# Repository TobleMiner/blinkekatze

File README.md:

Blinkekatze 😺
=============

This is a replacement PCB for one version of cat themed night lights available via various online retailers.

It adds a number of RGB LEDs, sensors and wireless connectivity, enabling an interactive light display synchronized over a large number of Blinkekatzen.

Inspired by the wonderful [derf](https://github.com/derf)

# Architecture

The Blinkekatze is comprised of three PCBs:
 - The main board (this directory)
 - The USB board (located in [/usb-board](/usb-board))
 - The original power- and mode-switch board from the nightlight

## Mainboard

The main board contains most elements critical to device operation. At its heart is an ESP32-C3 for control.

The ESP32-C3 is accompanied by the following peripherals:
 - 16 super bright, individually controllable RGB LEDs (effectively ~12bit RGB color control)
 - High precision battery gauge for accurate capacity tracking and runtime estimation
 - Accelerometer and barometer to detect user interaction
 - Ambient light sensor enabling automatic brightness control
 - Efficient buck-mode battery charger

The main board also includes a MEMS PDM microphone that could be used for audio synchronization of lighting effects.
However note the ESP32-C3 is missing hardware PDM to PCM conversion capability.

## USB board

The USB board replaces the original board used for charging in the nightlight. It offers USB connectivity to the
ESP32-C3 and contains two indicator LEDs visible through the bottom of the Blinkekatze.

To facilitate easy, solderless assembly mainboard and USB board are connected by a 5cm long 16 pin flat flex cable with opposite side contacts.

# Ordering PCBs

All PCBs required to build Blinkekatzen can be ordered fully assembled from JLCPCB. The necessary fabrication files are located in [/fab](/fab) for
the main board and [/usb-board/fab](/usb-board/fab). It is recommended to always use the latest revision available in those folders.  
When ordering the PCBs they should be ordered as 1.6mm 4 layers for the mainboard and 1.6mm 2 layers for the USB board.

## PCB assembly

In addition to the bare PCBs JLCPCB also offers an assembly service. The BOM and component centroid files required for assembly are also located in
[/fab](/fab) and [/usb-board/fab](/usb-board/fab) respectively.  
When ordering assembly for the main PCB cost can be reduced significantly by choosing to populate only the top side of the PCB and later assembling
the battery contacts (BTT1 and BTT2) on the bottom side by yourself manually. Those are the only parts on the bottom side of the PCB. Also microphone
U6 is best left unpopulated since a lack of proper PDM to PCM support on the ESP32-C3 makes it mostly unusable.

### Additional required electronic components

Apart from the components assembled by JLCPCB the following parts are required:  
 - 2x MYOUNG MY-18650-01 battery contacts (if not assembled by JLCPCB, see previous section)
 - 1x 5cm 16pin 0.5mm pitch flat flex cable (e.g. C5151983 on LCSC)
 - 1x 18650 battery (Samsung INR18650-35E recommended)

### JLCPCB assembly component availability

Sometimes components required for assembly are out of stock at JLCPCB. In this case the parts have to be ordered fist through
JLCPCB's parts preorder service. Usually all required parts can be preordered in small quantities and will be available within
a couple of days.

# Assembling the Blinkekatzen

## Preparing the PCB

If the battery contacts were not assembled through JLCPCB they need to be soldered. The overall fit of the battery is best with the
contacts installed as far apart as possible within the throughholes. Special care should be taken to ensure the battery contacts are
not soldered at an angle but lie flat on the PCB. Otherwise the battery might not snap into the contacts properly.

## Preparing the housing

In the first step the rubber boot needs to be removed. The puck containing all electronics can either be pulled out to the bottom or
first pushed into the puck and then removed.  
Next the transparent diffuser on top of the puck can be removed by undoing the three screws (relatively long and skinny #0 Phillips
head screwdriver required) and pulling up on the diffuser.  

## Removing the original PCBs

The original PCB is held in place with two screws. After undoing the screws the PCB can be pivoted to the side and the battery unplugged.  
The original USB board also needs to be removed by undoing the two screws holding it in place.  
Finally the PCB can be freed by desoldering the six connections on the original main PCB that go to the switch board in the bottom of the case.
Since the switch board will be reused desoldering rather than cutting the wire can save some time later.  

## Modifying the case

After removal of the original main PCB the case needs to be modified slightly to accommodate the new battery. To make space for the new battery
and battery holder snip out the two thin plastic walls with the half circle shaped cutouts the old battery was resting on using flush cutters.

## Installing the USB board

The first new component to be installed in the housing is the new USB board. Since this board will be installed with the USB connector and flat
flex connector facing down the flat flex cable needs to be connected to this board first. To connect the flat flex cable the latch on the
connector must be flipped up and the cable then inserted with the contacts facing down. The cable is then secured by closing the latch again.  
Now the USB board can be installed in the housing and secured in place with the two screws.

## Installing the new main PCB

As a first step the two outermost contacts of the ribbon cable earlier desoldered from the original main PCB are soldered to the power key header
J1 on the new main PCB (labeled PWR_ON and VBAT, polarity does not matter). Then the battery is installed (here polarity does very much matter). **NEVER**
may batteries without or with a damaged insulating sleeve be used with this device. The battery contacts will short out such batteries!  
After folding back the flat flex cable so it remains free and is not trapped under the battery the new main PCB is fixed in place with two screws.  
As a final step the flat flex cable is now installed into the flat flex connector on the new main PCB in the same manner as on the USB board.

## Firmware flashing

Please see [blinkekatze-firmware](https://github.com/TobleMiner/blinkekatze-firmware) for details on firmware flashing.

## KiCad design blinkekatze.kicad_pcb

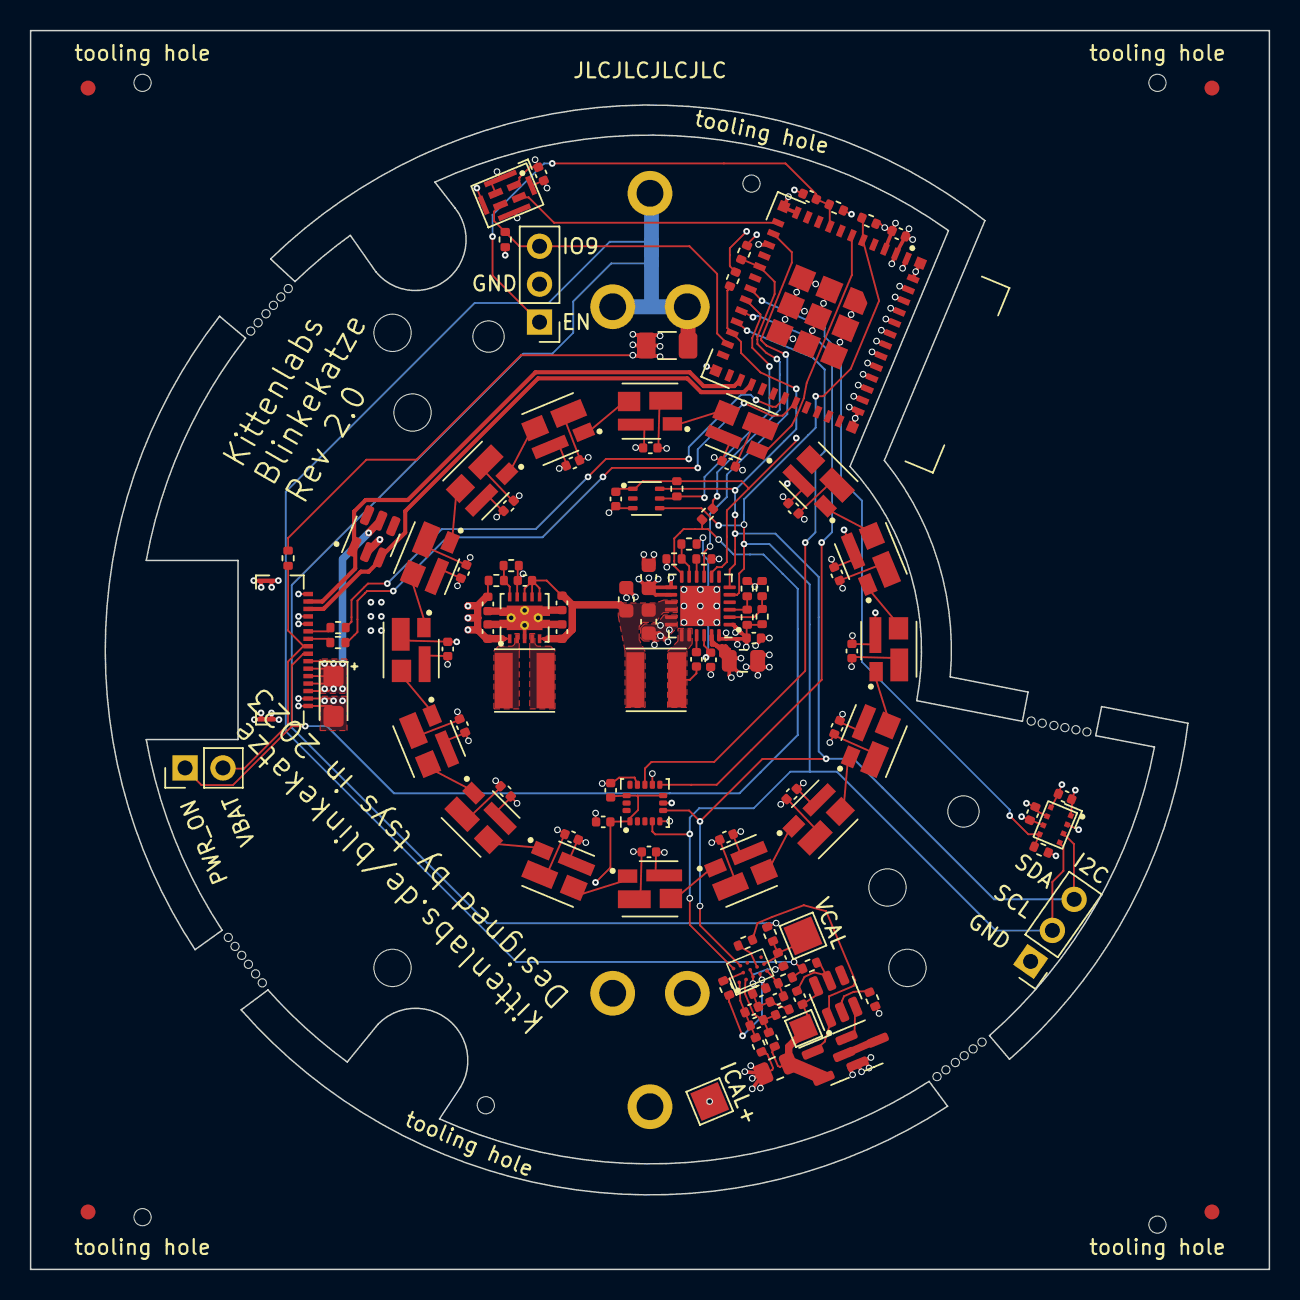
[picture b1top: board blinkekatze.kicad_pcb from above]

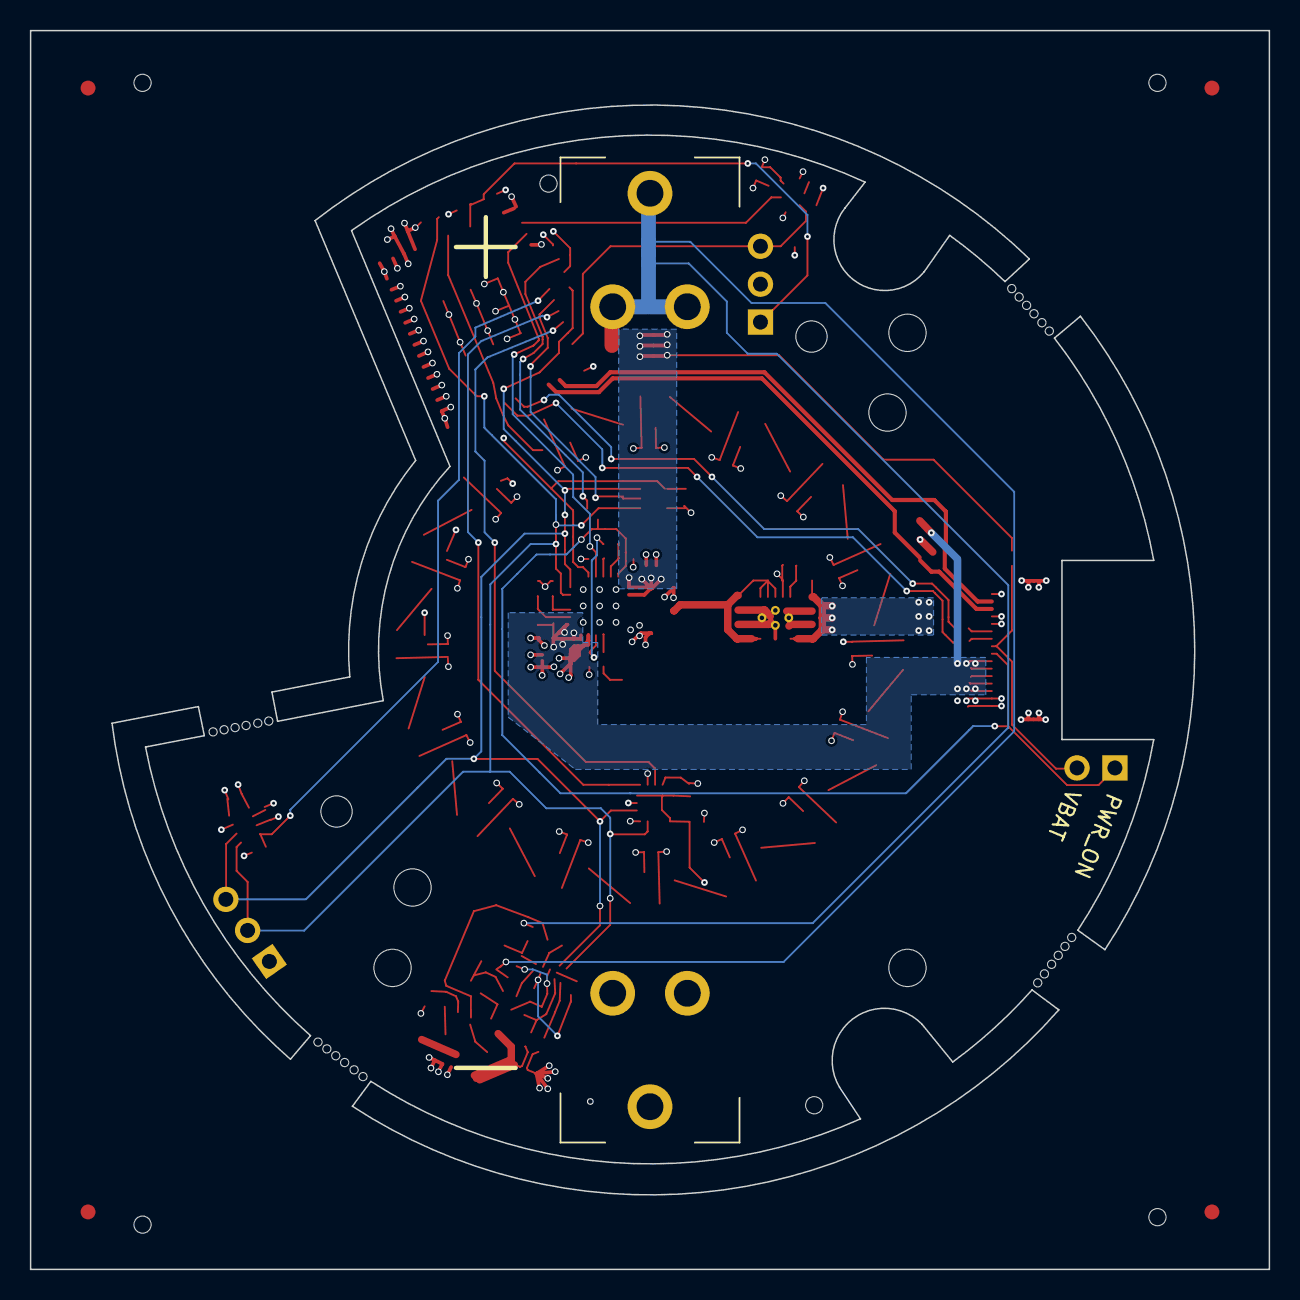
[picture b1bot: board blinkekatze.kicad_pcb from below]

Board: 4 copper layers, 83.0 x 83.0 mm, 122 parts (2 on the bottom side), 66 nets.

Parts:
BTT1: B+; MY-18650-01_flat-top
BTT2: B-; MY-18650-01_flat-top
C1, C2, C3, C4, C5, C6, C7, C8, C9, C10, C11, C12, C13, C14, C15, C16, C20, C21, C22, C23, C24, C26, C27, C73: 100nF; C_0402_1005Metric
C17: 10uF; CP_EIA-3216-18_Kemet-A
C18, C19, C25, C33, C66, C67, C68, C69, C70: 1uF; C_0402_1005Metric
C28: 22uF; C_0805_2012Metric
C29: 4.7uF; C_0402_1005Metric
C30, C31, C32: 10uF; C_0603_1608Metric
C65, C71, C72, C74, C75: 10uF; C_0402_1005Metric
D1, D2, D3, D4, D5, D6, D7, D8, D9, D10, D11, D12, D13, D14, D15, D16: SK6812MINI-012; XXXX12-X1
F1: 4A; Fuse_1206_3216Metric
H1: Left peg; MountingHole_2.1mm
H2: Right peg; MountingHole_2.1mm
H3: Left screw; MountingHole_2.5mm
H4: Right screw; MountingHole_2.5mm
H5, H6: Tooling hole; ToolingHole_JLCSMT
H7: LU; MountingHole_2.5mm
H8: RL; MountingHole_2.5mm
H9: LL; MountingHole_2.5mm
J1: Power key; PinHeader_1x02_P2.54mm_Vertical
J2: Strapping; PinHeader_1x03_P2.54mm_Vertical
J3: I2C; PinHeader_1x03_P2.54mm_Vertical
J4: USB board; 0.5K-QX-16PWB_16Pin_0.5mm
L2, L4: 2.2uH; L_Taiyo-Yuden_MD-4040
Q1, Q2: AO3400A; SOT-23
R1, R9, R13, R14, R15, R16, R17, R18, R21, R22, R43: 10k; R_0402_1005Metric
R2, R5, R6, R7, R10, R11, R12: 100R; R_0402_1005Metric
R3: 220R; R_0402_1005Metric
R4: 10mR; R_0805_2012Metric
R8: 1k; R_0402_1005Metric
R19, R20: 330; R_0402_1005Metric
R23, R44: 100k; R_0402_1005Metric
R45, R46: 4.7k; R_0402_1005Metric
R48: 0R; R_0402_1005Metric
R49: DNP; R_0402_1005Metric
TP3: ICAL+; TestPoint_Pad_2.0x2.0mm
TP4: VCAL; TestPoint_Pad_2.0x2.0mm
TP5: ICAL-; TestPoint_Pad_1.5x1.5mm
U1: ESP32-C3-MINI-1
U2: BQ27546; DSBGA-15_BQ27546_I2C_1.95x2.6mm_P0.5mm
U3: SRV05-4; SOT-23-6
U4: FM2113; SOT-23-6
U5: SPL06-001; LGA-8_2x2.5mm_P0.65mm
U6: ST_HCLGA-4LD_3x4mm
U7: LTR-303ALS-01; Lite-On_LTR-303ALS-01
U8: BQ24295; QFN-24-1EP_4x4mm_P0.5mm_EP2.7x2.7mm
U9: TPS63001; Texas_DRC0010J_ThermalVias.3
U10: LIS3DH; LGA-16_3x3mm_P0.5mm_LayoutBorder3x5y

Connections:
+3V3: C18.2, C19.1, C65.1, C67.1, C68.1, C69.2, C70.1, C74.2, C75.2, R21.1, R22.1, R43.1, R44.1, R45.1, R46.1, R48.1, U1.3 (3V3), U5.2 (CSB), U5.6 (VDDIO), U5.8 (VDD), U6.1 (VDD), U7.1 (VDD), U8.8 (OTG), U9.1 (VOUT), U10.1 (VDD_IO), U10.8 (CS), U10.14 (VDD)
+BATT: BTT1.1, F1.1, R7.1, R10.1, R11.1
/Battery/BAT+: C32.1, F1.2, R2.2, U8.13 (BAT), U8.14 (BAT)
/Battery/DSG: R12.2, U2.D2 (CE)
/Battery/SCL: J3.2, R46.2, U1.5 (IO2), U2.A3 (SCL), U5.4 (SCK), U7.4 (SCL), U8.5 (SCL), U10.4 (SCL/SPC)
/Battery/SDA: J3.3, R45.2, U1.22 (IO8), U2.B3 (SDA), U5.3 (SDA), U7.6 (SDA), U8.6 (SDA), U10.6 (SDA/SDI/SDO)
/Charger/PWR_ON: J1.1, J4.9, R1.1, U8.12 (QON)
/Charger/VLED: C1.2, C2.2, C3.2, C4.2, C5.2, C6.2, C7.2, C8.2, C9.2, C10.2, C11.2, C12.2, C13.2, C14.2, C15.2, C16.2, C28.1, D1.2 (VDD), D2.2 (VDD), D3.2 (VDD), D4.2 (VDD), D5.2 (VDD), D6.2 (VDD), D7.2 (VDD), D8.2 (VDD), D9.2 (VDD), D10.2 (VDD), D11.2 (VDD), D12.2 (VDD), D13.2 (VDD), D14.2 (VDD), D15.2 (VDD), D16.2 (VDD), U8.23 (PMID)
/Charger/VSYS: C30.1, C31.1, C71.2, C72.2, C73.2, L2.2, U8.15 (SYS), U8.16 (SYS), U9.5 (VIN), U9.6 (EN), U9.7 (PS/SYNC), U9.8 (VINA)
/Charger/~CHARGE_ENABLE: U1.13 (IO1), U8.9 (~CE)
/LEDs/DIN: D12.1 (DIN), U1.6 (IO3)
/Logic/EN: C66.2, J2.1, R44.2, U1.8 (EN)
/Logic/IO9: J2.3, R43.2, U1.23 (IO9), U6.3 (CLK)
/Logic/LED1: J4.6, R20.1
/Logic/LED2: J4.7, R19.1
/Logic/USB_D+: J4.3, U1.27 (IO19/D+), U3.3 (IO2)
/Logic/USB_D-: J4.2, U1.26 (IO18/D-), U3.1 (IO1)
/USB/VBAT: J1.2, J4.8, R2.1
GND: C1.1, C2.1, C3.1, C4.1, C5.1, C6.1, C7.1, C8.1, C9.1, C10.1, C11.1, C12.1, C13.1, C14.1, C15.1, C16.1, C17.2, C18.1, C19.2, C28.2, C29.2, C30.2, C31.2, C32.2, C33.1, C65.2, C66.1, C67.2, C68.2, C69.1, C70.2, C71.1, C72.1, C73.1, C74.1, C75.1, D1.4 (VSS), D2.4 (VSS), D3.4 (VSS), D4.4 (VSS), D5.4 (VSS), D6.4 (VSS), D7.4 (VSS), D8.4 (VSS), D9.4 (VSS), D10.4 (VSS), D11.4 (VSS), D12.4 (VSS), D13.4 (VSS), D14.4 (VSS), D15.4 (VSS), D16.4 (VSS), J2.2, J3.1, J4.1, J4.4, J4.5, J4.15, J4.16, J4.MP (MountPin), Q2.2 (S), R3.2, R8.1, R14.2, R15.2, R16.2, R23.2, R49.2, U1.1 (GND), U1.2 (GND), U1.11 (GND), U1.14 (GND), U1.36 (GND), U1.37 (GND), U1.38 (GND), U1.39 (GND), U1.40 (GND), U1.41 (GND), U1.42 (GND), U1.43 (GND), U1.44 (GND), U1.45 (GND), U1.46 (GND), U1.47 (GND), U1.48 (GND), U1.49 (GND), U1.50 (GND), U1.51 (GND), U1.52 (GND), U1.53 (GND), U3.2 (VN), U5.1 (GND), U5.7 (GND), U6.2 (L/R), U6.5 (GND), U7.3 (GND), U8.17 (PGND), U8.18 (PGND), U8.25 (PGND), U9.3 (PGND), U9.9 (GND), U9.11 (PGND), U10.5 (GND), U10.7 (SDO/SA0), U10.10 (GND), U10.12 (GND)
GND1: BTT2.1, C20.1, C22.2, C23.2, C24.2, C25.1, R4.1, R5.1, TP3.1, U2.C1 (VSS), U2.C2 (VSS)
unnamed: C27.1, L2.1, U8.19 (SW), U8.20 (SW)
unnamed: D1.1 (DIN), D16.3 (DOUT)
unnamed: D1.3 (DOUT), D2.1 (DIN)
unnamed: D2.3 (DOUT), D3.1 (DIN)
unnamed: D3.3 (DOUT), D4.1 (DIN)
unnamed: D4.3 (DOUT), D5.1 (DIN)
unnamed: D5.3 (DOUT), D6.1 (DIN)
unnamed: D6.3 (DOUT), D7.1 (DIN)
unnamed: D7.3 (DOUT), D8.1 (DIN)
unnamed: D8.3 (DOUT), D9.1 (DIN)
unnamed: D9.3 (DOUT), D10.1 (DIN)
unnamed: D10.3 (DOUT), D11.1 (DIN)
unnamed: D12.3 (DOUT), D13.1 (DIN)
unnamed: D13.3 (DOUT), D14.1 (DIN)
unnamed: D14.3 (DOUT), D15.1 (DIN)
unnamed: D15.3 (DOUT), D16.1 (DIN)
unnamed: Q1.3 (D), Q2.3 (D)
unnamed: Q1.1 (G), R12.1, U4.1 (DO)
unnamed: C26.1, Q1.2 (S), R4.2, R6.1, TP5.1, U4.6 (VSS)
unnamed: Q2.1 (G), U4.3 (CO)
unnamed: U1.12 (IO0), U6.4 (DATA)
unnamed: R21.2, U1.18 (IO4), U5.5 (SDO)
unnamed: R22.2, U1.19 (IO5), U7.5 (INT)
unnamed: U1.20 (IO6), U10.9 (INT2)
unnamed: U1.21 (IO7), U10.11 (INT1)
unnamed: R1.2, R23.1, U1.16 (IO10)
unnamed: R20.2, U1.30 (RXD0)
unnamed: R19.2, U1.31 (TXD0)
unnamed: C23.1, R7.2, TP4.1, U2.E2 (BAT)
unnamed: C24.1, R10.2, U2.E1 (REGIN)
unnamed: C21.2, C22.1, R6.2, U2.B1 (SRN)
unnamed: C20.2, C21.1, R5.2, U2.A1 (SRP)
unnamed: R9.1, U2.B2 (TS)
unnamed: C25.2, R9.2, U2.D1 (VCC)
unnamed: C26.2, R11.2, U4.5 (VDD)
unnamed: R8.2, U4.2 (VM)
unnamed: C27.2, U8.21 (BTST)
unnamed: R15.1, R17.2, U8.2 (D+)
unnamed: R16.1, R18.2, U8.3 (D-)
unnamed: R3.1, U8.10 (ILIM)
unnamed: C29.1, R13.2, U8.22 (REGN)
unnamed: R13.1, R14.1, U8.11 (TS)
unnamed: R48.2, R49.1, U9.10 (FB)
unnamed: L4.1, U9.4 (L1)
unnamed: L4.2, U9.2 (L2)
VBUS: C17.1, C33.2, J4.10, J4.11, J4.12, J4.13, J4.14, R17.1, R18.1, U3.5 (VP), U8.1 (VBUS), U8.24 (VBUS)

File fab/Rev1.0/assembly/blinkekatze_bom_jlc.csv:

"Comment","Designator","Footprint","LCSC Part #"
"B+","BTT1","MY-18650-01","C2979183"
"B-","BTT2","MY-18650-01","C2979183"
"100nF","C1,C2,C3,C4,C5,C6,C7,C8,C9,C10,C11,C12,C13,C14,C15,C16,C73,C20,C21,C22,C23,C24,C26,C27","C_0402_1005Metric","C1525"
"10uF","C17","CP_EIA-3216-18_Kemet-A","C7171"
"1uF","C18,C19,C66,C67,C68,C69,C70,C25,C33","C_0402_1005Metric","C52923"
"22uF","C28","C_0805_2012Metric","C45783"
"4.7uF","C29","C_0402_1005Metric","C23733"
"10uF","C30,C31,C32","C_0603_1608Metric","C19702"
"10uF","C65,C71,C72,C74,C75","C_0402_1005Metric","C15525"
"SK6812MINI-012","D1,D2,D3,D4,D5,D6,D7,D8,D9,D10,D11,D12,D13,D14,D15,D16","XXXX12-X1","C2886570"
"4A","F1","Fuse_1206_3216Metric","C187596"
"2.2uH","L4,L2","L_Taiyo-Yuden_MD-4040","C98361"
"AO3400A","Q1,Q2","SOT-23","C20917"
"10k","R1,R43,R9,R13,R14,R15,R16,R17,R18","R_0402_1005Metric","C25744"
"100R","R2,R5,R6,R7,R10,R11,R12","R_0402_1005Metric","C25076"
"150R","R3","R_0402_1005Metric","C25082"
"10mR","R4","R_0805_2012Metric","C5185583"
"1k","R8","R_0402_1005Metric","C11702"
"330","R19,R20","R_0402_1005Metric","C25104"
"100k","R44","R_0402_1005Metric","C25741"
"4.7k","R45,R46","R_0402_1005Metric","C25900"
"0R","R48","R_0402_1005Metric","C17168"
"ESP32-C3-MINI-1","U1","ESP32-C3-MINI-1","C2838502"
"BQ27546","U2","DSBGA-15_BQ27546_I2C_1.95x2.6mm_P0.5mm","C528629"
"SRV05-4","U3","SOT-23-6","C85364"
"FM2113","U4","SOT-23-6","C2832124"
"SPL06-001","U5","LGA-8_2x2.5mm_P0.65mm","C2684428"
"~","U6","ST_HCLGA-4LD_3x4mm","C503097"
"LTR-303ALS-01","U7","Lite-On_LTR-303ALS-01","C364577"
"BQ24295","U8","QFN-24-1EP_4x4mm_P0.5mm_EP2.7x2.7mm","C165144"
"TPS63001","U9","Texas_DRC0010J_ThermalVias.3","C28060"
"LIS3DH","U10","LGA-16_3x3mm_P0.5mm_LayoutBorder3x5y","C15134"

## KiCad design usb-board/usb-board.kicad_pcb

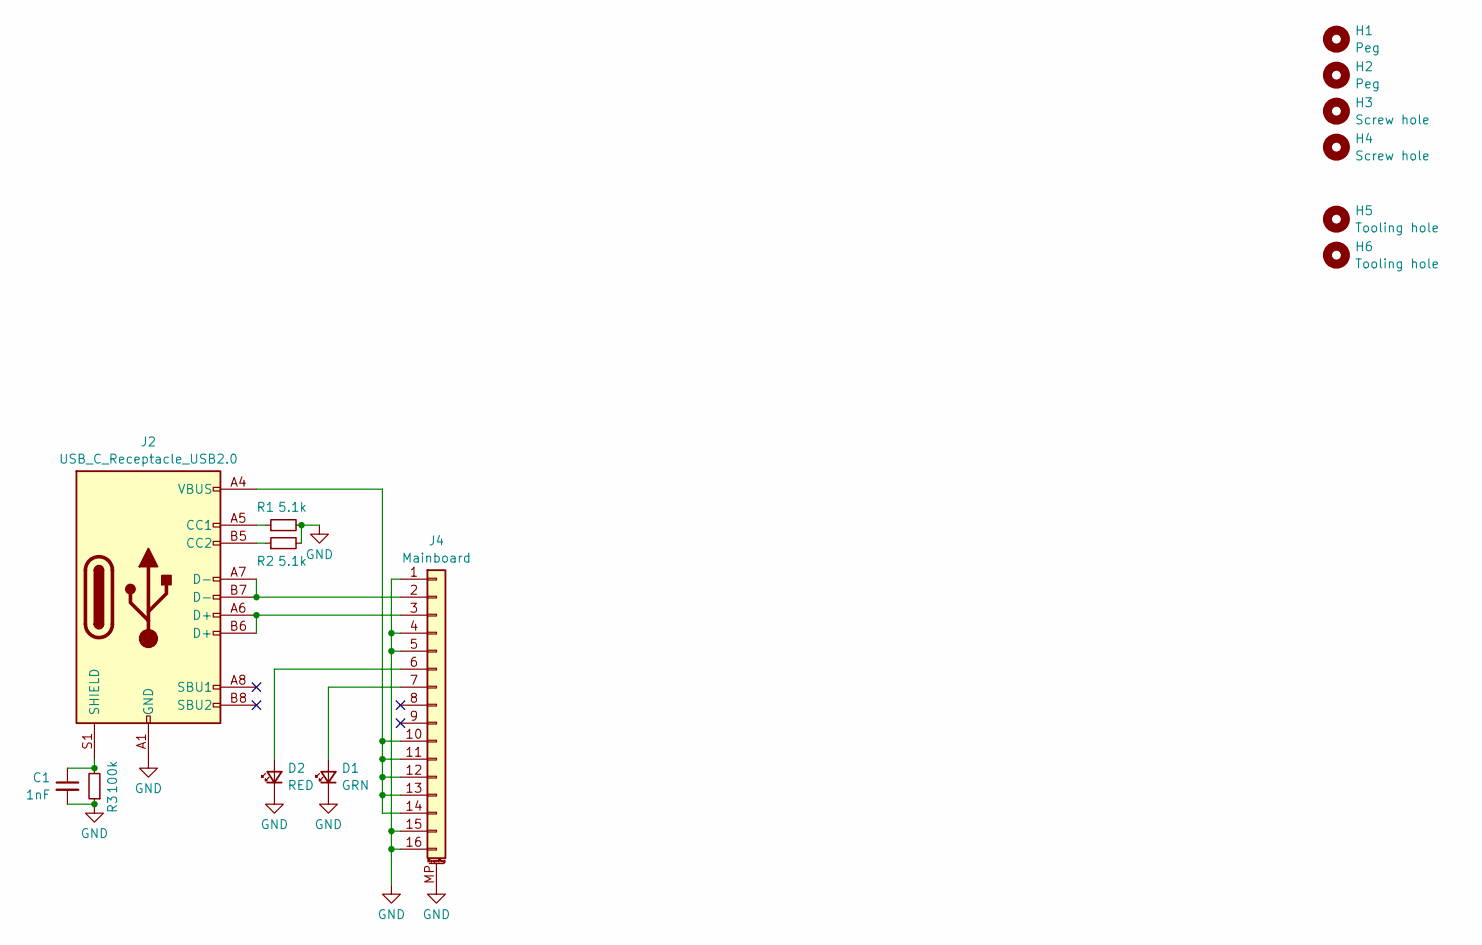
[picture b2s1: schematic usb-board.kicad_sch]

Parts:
C1: 1nF; C_1206_3216Metric; LCSC C9196
D1: GRN; LED_0603_1608Metric; LCSC C72043
D2: RED; LED_0603_1608Metric; LCSC C2286
H1, H2: Peg; MountingHole_2.1mm
H3, H4: Screw hole; MountingHole_2.5mm
H5, H6: Tooling hole; ToolingHole_JLCSMT
J2: USB_C_Receptacle_USB2.0; USB_C_Receptacle_Palconn_UTC16-G; LCSC C167321
J4: Mainboard; 0.5K-QX-16PWB_16Pin_0.5mm; LCSC C2919481
R1, R2: 5.1k; R_0402_1005Metric; LCSC C25905
R3: 100k; R_0805_2012Metric; LCSC C149504

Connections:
GND: C1.2, D1.1 (K), D2.1 (K), J2.A1 (GND), J2.A12 (GND), J2.B1 (GND), J2.B12 (GND), R1.2, R2.2, R3.1; also elsewhere on the board
unnamed 1: D1.2 (A); also elsewhere on the board
unnamed 2: D2.2 (A); also elsewhere on the board
unnamed: J2.A5 (CC1), R1.1
unnamed: J2.B5 (CC2), R2.1
unnamed: C1.1, J2.S1 (SHIELD), R3.2
unnamed 6: J2.A7 (D-), J2.B7 (D-); also elsewhere on the board
unnamed 7: J2.A6 (D+), J2.B6 (D+); also elsewhere on the board
unnamed 8: J2.A4 (VBUS), J2.A9 (VBUS), J2.B4 (VBUS), J2.B9 (VBUS); also elsewhere on the board

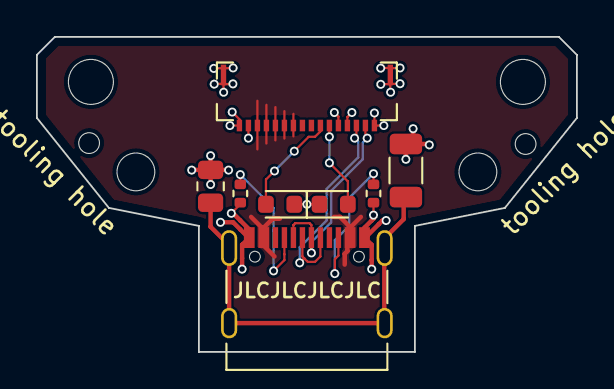
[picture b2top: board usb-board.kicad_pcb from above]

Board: 2 copper layers, 30.0 x 17.5 mm, 14 parts (0 on the bottom side), 9 nets.

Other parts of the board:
J3: Mainboard; 0.5K-QX-16PWB_16Pin_0.5mm

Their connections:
GND: J3.1, J3.4, J3.5, J3.15, J3.16, J3.MP (MountPin); also elsewhere on the board
unnamed 1: J3.7; also elsewhere on the board
unnamed 2: J3.6; also elsewhere on the board
unnamed 6: J3.2; also elsewhere on the board
unnamed 7: J3.3; also elsewhere on the board
unnamed 8: J3.10, J3.11, J3.12, J3.13, J3.14; also elsewhere on the board

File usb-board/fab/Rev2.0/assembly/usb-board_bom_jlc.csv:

"Comment","Designator","Footprint","LCSC Part #"
"1nF","C1","C_1206_3216Metric","C9196"
"GRN","D1","LED_0603_1608Metric","C72043"
"RED","D2","LED_0603_1608Metric","C2286"
"USB_C_Receptacle_USB2.0","J2","USB_C_Receptacle_Palconn_UTC16-G","C167321"
"Mainboard","J3","0.5K-QX-16PWB_16Pin_0.5mm","C2919481"
"5.1k","R1,R2","R_0402_1005Metric","C25905"
"100k","R3","R_0805_2012Metric","C149504"

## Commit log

2023-09-08 Add gauge schematic and partial charger schematic
2023-09-08 Fix duplicate pin assignment on pressure sensor
2023-09-08 Finish preliminary charger and logic schematic
2023-09-08 Aesthetic top level schematic fixes
2023-09-10 Add list of 1S charger chips
2023-09-11 Finish rough layout
2023-09-11 Add 3D model to battery gauge
2023-09-11 Hide silkscreen designators
2023-09-11 JLCPCB DFM
2023-09-11 Add accelerometer
2023-09-11 Add copper fill keepouts below poorly shielded inductors
2023-09-11 Add pin 1 marker to ambient light sensor and accelerometer
2023-09-11 Add I2C test connector
2023-09-11 Add battery polarity indicators
2023-09-11 Remove duplicate pin 36 from ESP32-C3-MINI-1
2023-09-11 Reduce battery protection IC VDD impedance
    Reduce from 470R to 100R in line with manufacturers recommendation
2023-09-11 Update ESP32-C3-MINI-1 symbol in schematic
2023-09-11 Fix incorrect vertical pad spacing on SK6812-MINI-X1 footprint
2023-09-11 Update SK6812-MINI-X1 footprints
2023-09-11 Add simple USB board replacement
2023-09-11 usb-board: improve VBUS connection
2023-09-11 Add pin 1 marker to barometric pressure sensor
2023-09-13 Add informational comment on input current limit to schematic
2023-10-11 lib: add flat-top variant of MY-18650-01 battery holder
2023-10-11 usb-board: add silkscreen markings
2023-10-11 battery: use flat top battery holder
2023-10-11 logic: connect pressure sensor via I2C
2023-10-11 Add additional mounting holes for micro USB cat nightlight variant
2023-10-11 Partial rip-up of old design
2023-10-15 Add HDGC FPC lib
2023-10-15 Relayout board to fit constraints of Micro USB Blinkekatzen
2023-10-15 DFM and 2A input current limit
2023-10-15 Change mainboard connector to FFC type
2023-10-15 usb-board: fix FFC pinout
2023-10-15 usb-board: update silkscreen designators
    - Remove second JLCJLCJLCJLC designator
    - Change revision indicator to Rev2.0
2023-10-15 usb-board: add fabrication files
2023-10-15 logic: update LCSC partnumbers
2023-10-15 Update copper fill
2023-10-15 Add fabrication files
2023-11-25 Add FFC 3D model
2023-11-29 Add minimal README
2023-11-29 Add schematic exports
2023-11-29 Flesh out readme a bit
2024-01-21 README: provie more detailed assembly instructions
2024-06-03 README: add photo of mainboard installed in base
